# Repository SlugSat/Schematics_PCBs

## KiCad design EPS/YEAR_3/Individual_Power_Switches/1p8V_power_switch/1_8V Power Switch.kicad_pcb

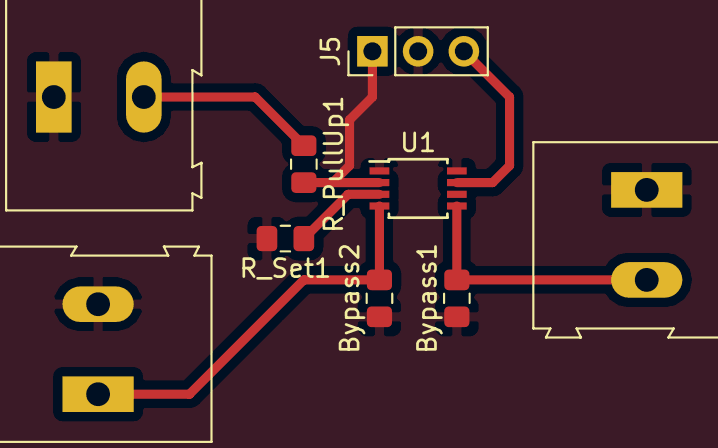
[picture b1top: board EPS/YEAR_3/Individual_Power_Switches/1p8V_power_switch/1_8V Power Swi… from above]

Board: 2 copper layers, 9 parts (0 on the bottom side), 7 nets.

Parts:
Bypass1, Bypass2: 1uF; C_0805_2012Metric_Pad1.15x1.40mm_HandSolder
J2, J3, J4: Screw_Terminal_01x02; TerminalBlock_Altech_AK300-2_P5.00mm
J5: Conn_01x03_Male; PinHeader_1x03_P2.54mm_Vertical
R_PullUp1: 10k; R_0805_2012Metric_Pad1.15x1.40mm_HandSolder
R_Set1: x; R_0805_2012Metric_Pad1.15x1.40mm_HandSolder
U1: MAX14523A; TSSOP-8_3x3mm_P0.65mm

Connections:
GND: Bypass1.1, Bypass2.1, J2.1, J3.2, J4.1, J5.2, R_Set1.2, U1.1, U1.6, U1.8
unnamed: Bypass1.2, J4.2, U1.5
unnamed: Bypass2.2, J3.1, U1.4
unnamed: J2.2, R_PullUp1.1
unnamed: J5.1, R_PullUp1.2, U1.2
unnamed: J5.3, U1.7
unnamed: R_Set1.1, U1.3

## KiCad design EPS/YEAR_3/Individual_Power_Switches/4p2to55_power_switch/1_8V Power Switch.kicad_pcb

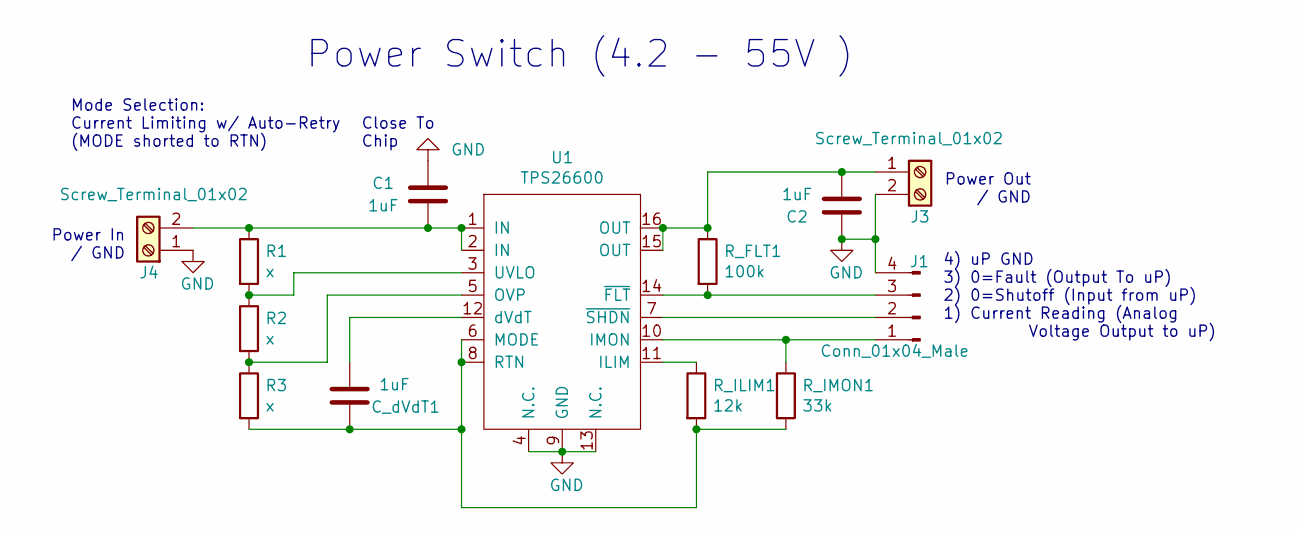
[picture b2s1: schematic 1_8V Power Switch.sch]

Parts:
C1, C2: 1uF; C_0805_2012Metric_Pad1.15x1.40mm_HandSolder
C_dVdT1: 1uF; C_0805_2012Metric_Pad1.15x1.40mm_HandSolder
J1: Conn_01x04_Male; PinSocket_1x04_P2.54mm_Vertical
J3, J4: Screw_Terminal_01x02; TerminalBlock_MetzConnect_Type094_RT03502HBLU_1x02_P5.00mm_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
R1, R2, R3: x; R_0805_2012Metric_Pad1.15x1.40mm_HandSolder
R_FLT1: 100k; R_0805_2012Metric_Pad1.15x1.40mm_HandSolder
R_ILIM1: 12k; R_0805_2012Metric_Pad1.15x1.40mm_HandSolder
R_IMON1: 33k; R_0805_2012Metric_Pad1.15x1.40mm_HandSolder
U1: TPS26600; TSSOP-16_4.4x5mm_P0.65mm

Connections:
GND: C1.2, C2.1, J1.4, J3.2, J4.1, U1.4 (N.C.), U1.9 (GND), U1.13 (N.C.)
unnamed: C1.1, J4.2, R1.1, U1.1 (IN), U1.2 (IN)
unnamed: C2.2, J3.1, R_FLT1.1, U1.15 (OUT), U1.16 (OUT)
unnamed: C_dVdT1.1, R3.2, R_ILIM1.2, R_IMON1.2, U1.6 (MODE), U1.8 (RTN)
unnamed: C_dVdT1.2, U1.12 (dVdT)
unnamed: J1.1, R_IMON1.1, U1.10 (IMON)
unnamed: J1.2, U1.7 (~SHDN)
unnamed: J1.3, R_FLT1.2, U1.14 (~FLT)
unnamed: R1.2, R2.1, U1.3 (UVLO)
unnamed: R2.2, R3.1, U1.5 (OVP)
unnamed: R_ILIM1.1, U1.11 (ILIM)

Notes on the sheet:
4) uP GND 3) 0=Fault (Output To uP) 2) 0=Shutoff (Input from uP) 1) Current Reading (Analog Voltage Output to uP)
Power Out / GND
Power In / GND
Power Switch (4.2 - 55V )
Mode Selection: Current Limiting w/ Auto-Retry (MODE shorted to RTN)
Close To Chip

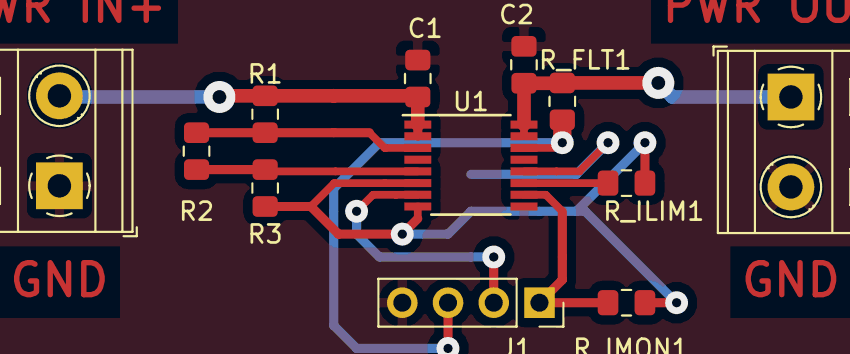
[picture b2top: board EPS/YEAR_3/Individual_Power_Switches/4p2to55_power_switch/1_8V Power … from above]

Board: 2 copper layers, 13 parts (1 on the bottom side), 11 nets.

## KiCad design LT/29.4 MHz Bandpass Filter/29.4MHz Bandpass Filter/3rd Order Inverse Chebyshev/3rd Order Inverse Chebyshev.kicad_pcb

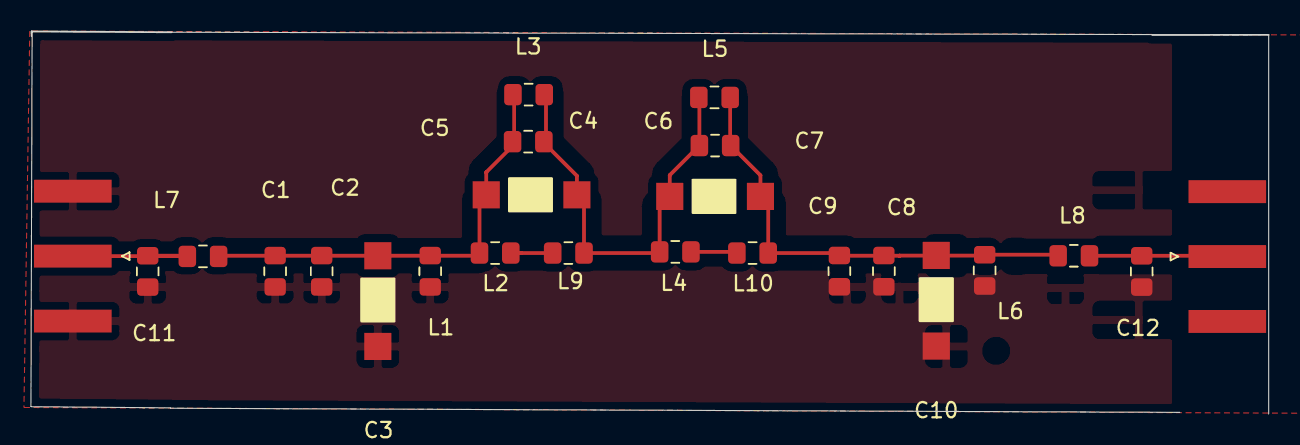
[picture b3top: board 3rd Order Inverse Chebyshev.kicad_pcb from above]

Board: 2 copper layers, 81.0 x 25.0 mm, 24 parts (0 on the bottom side), 8 nets.

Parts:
C1: 560p; C_0805_2012Metric_Pad1.15x1.40mm_HandSolder
C2, C9: 56pF; C_0805_2012Metric_Pad1.15x1.40mm_HandSolder
C3, C5, C7, C10: No Connect; Variable Capacitor
C4: 18pF; C_0805_2012Metric_Pad1.15x1.40mm_HandSolder
C6: 43pF; C_0805_2012Metric_Pad1.15x1.40mm_HandSolder
C8: 560pF; C_0805_2012Metric_Pad1.15x1.40mm_HandSolder
C11, C12: No Connect; C_0805_2012Metric_Pad1.15x1.40mm_HandSolder
J1, J2: Conn_Coaxial; SMA_Amphenol_132289_EdgeMount
L1, L6: 47nH; L_0805_2012Metric_Pad1.15x1.40mm_HandSolder
L2: 680nH; L_0805_2012Metric_Pad1.15x1.40mm_HandSolder
L3, L5: No Connect; L_0805_2012Metric_Pad1.15x1.40mm_HandSolder
L4: 1.5uH; L_0805_2012Metric_Pad1.15x1.40mm_HandSolder
L7, L8: Shorted Connection; L_0805_2012Metric_Pad1.15x1.40mm_HandSolder
L9: 6.8nH; L_0805_2012Metric_Pad1.15x1.40mm_HandSolder
L10: 72nH; L_0805_2012Metric_Pad1.15x1.40mm_HandSolder

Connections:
GND: C1.2, C2.2, C3.2, C8.2, C9.2, C10.2, C11.2, C12.2, J1.2, J2.2, L1.2, L6.2
unnamed: C1.1, C2.1, C3.1, C4.2, C5.1, L1.1, L2.1, L3.1, L7.2
unnamed: C4.1, C5.2, C6.2, C7.1, L3.2, L4.1, L5.1, L9.2
unnamed: C6.1, C7.2, C8.1, C9.1, C10.1, L5.2, L6.1, L8.1, L10.2
unnamed: C11.1, J1.1, L7.1
unnamed: C12.1, J2.1, L8.2
unnamed: L2.2, L9.1
unnamed: L4.2, L10.1

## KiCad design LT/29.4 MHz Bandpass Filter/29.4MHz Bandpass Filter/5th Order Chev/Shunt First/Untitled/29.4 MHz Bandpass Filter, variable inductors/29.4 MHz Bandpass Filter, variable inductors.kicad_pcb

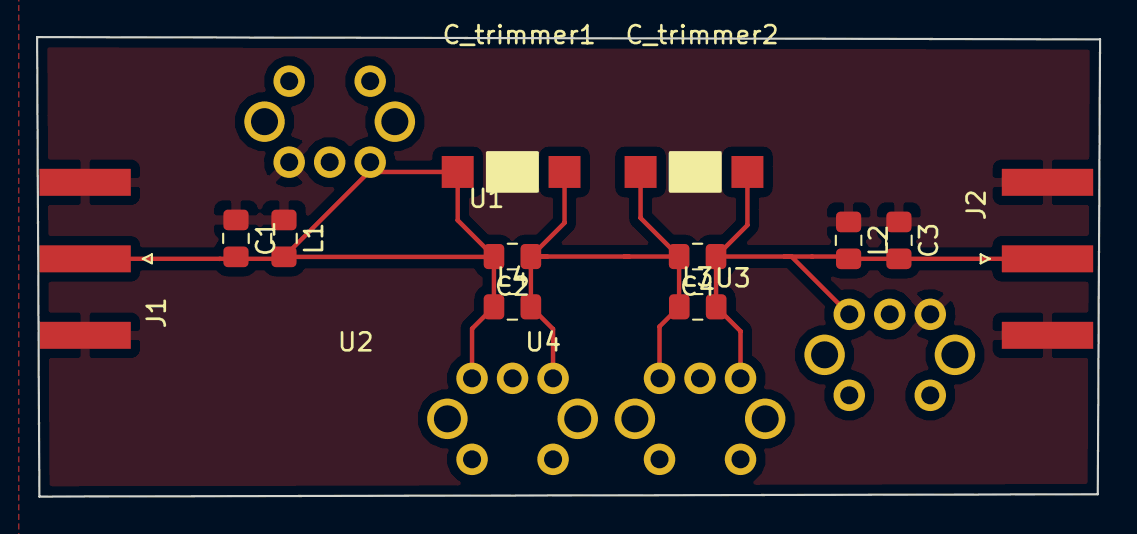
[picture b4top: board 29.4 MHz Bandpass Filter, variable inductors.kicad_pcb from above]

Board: 2 copper layers, 59.1 x 25.5 mm, 16 parts (0 on the bottom side), 4 nets.

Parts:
C1, C2, C3, C4: C; C_0805_2012Metric_Pad1.15x1.40mm_HandSolder
C_trimmer1, C_trimmer2: C_Variable; Variable Capacitor
J1, J2: Conn_Coaxial; SMA_Amphenol_132289_EdgeMount
L1: L_hold1; L_0805_2012Metric_Pad1.15x1.40mm_HandSolder
L2: L_hold2; L_0805_2012Metric_Pad1.15x1.40mm_HandSolder
L3: L_hold3; L_0805_2012Metric_Pad1.15x1.40mm_HandSolder
L4: L_hold1.5; L_0805_2012Metric_Pad1.15x1.40mm_HandSolder
U1, U2, U3, U4: LM3-IND; IND_trimmer_7M3

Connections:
GND: C1.1, C3.1, J1.2, J2.2, L1.1, L2.1, U1.3, U3.3
unnamed: C1.2, C2.2, C_trimmer1.2, J1.1, L1.2, L4.1, U1.1, U2.1
unnamed: C2.1, C4.2, C_trimmer1.1, C_trimmer2.2, L3.1, L4.2, U2.3, U4.1
unnamed: C3.2, C4.1, C_trimmer2.1, J2.1, L2.2, L3.2, U3.1, U4.3

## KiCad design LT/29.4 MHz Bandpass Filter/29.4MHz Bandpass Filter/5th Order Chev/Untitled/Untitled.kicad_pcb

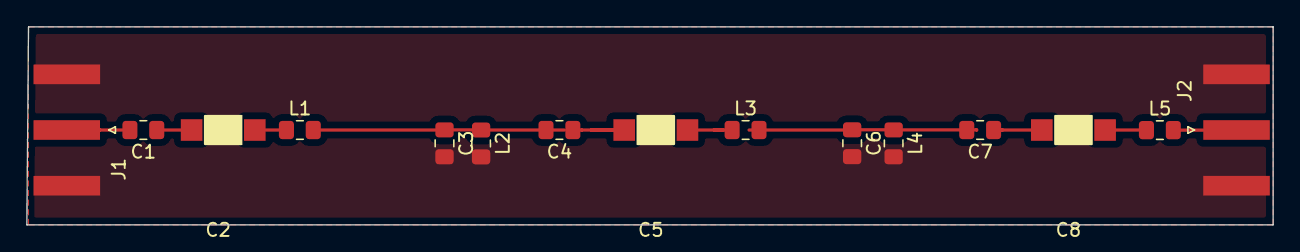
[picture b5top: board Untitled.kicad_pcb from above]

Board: 2 copper layers, 95.1 x 15.1 mm, 15 parts (0 on the bottom side), 11 nets.

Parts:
C1, C7: 3.6pF; C_0805_2012Metric_Pad1.15x1.40mm_HandSolder
C2, C5, C8: C_Variable; Variable Capacitor
C3, C4: 2.4pF; C_0805_2012Metric_Pad1.15x1.40mm_HandSolder
C6: 1.8nH; C_0805_2012Metric_Pad1.15x1.40mm_HandSolder
J1, J2: Conn_Coaxial; SMA_Amphenol_132289_EdgeMount
L1, L5: 8.2uH; L_0805_2012Metric_Pad1.15x1.40mm_HandSolder
L2: 16uH; L_0805_2012Metric_Pad1.15x1.40mm_HandSolder
L3: 12uH; L_0805_2012Metric_Pad1.15x1.40mm_HandSolder
L4: 16nH; L_0805_2012Metric_Pad1.15x1.40mm_HandSolder

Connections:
GND: C3.2, C6.2, J1.2, J2.2, L2.2, L4.2
unnamed: C1.1, C2.1
unnamed: C1.2, J1.1
unnamed: C2.2, L1.1
unnamed: C3.1, C4.2, L1.2, L2.1
unnamed: C4.1, C5.1
unnamed: C5.2, L3.1
unnamed: C6.1, C7.2, L3.2, L4.1
unnamed: C7.1, C8.1
unnamed: C8.2, L5.1
unnamed: J2.1, L5.2
